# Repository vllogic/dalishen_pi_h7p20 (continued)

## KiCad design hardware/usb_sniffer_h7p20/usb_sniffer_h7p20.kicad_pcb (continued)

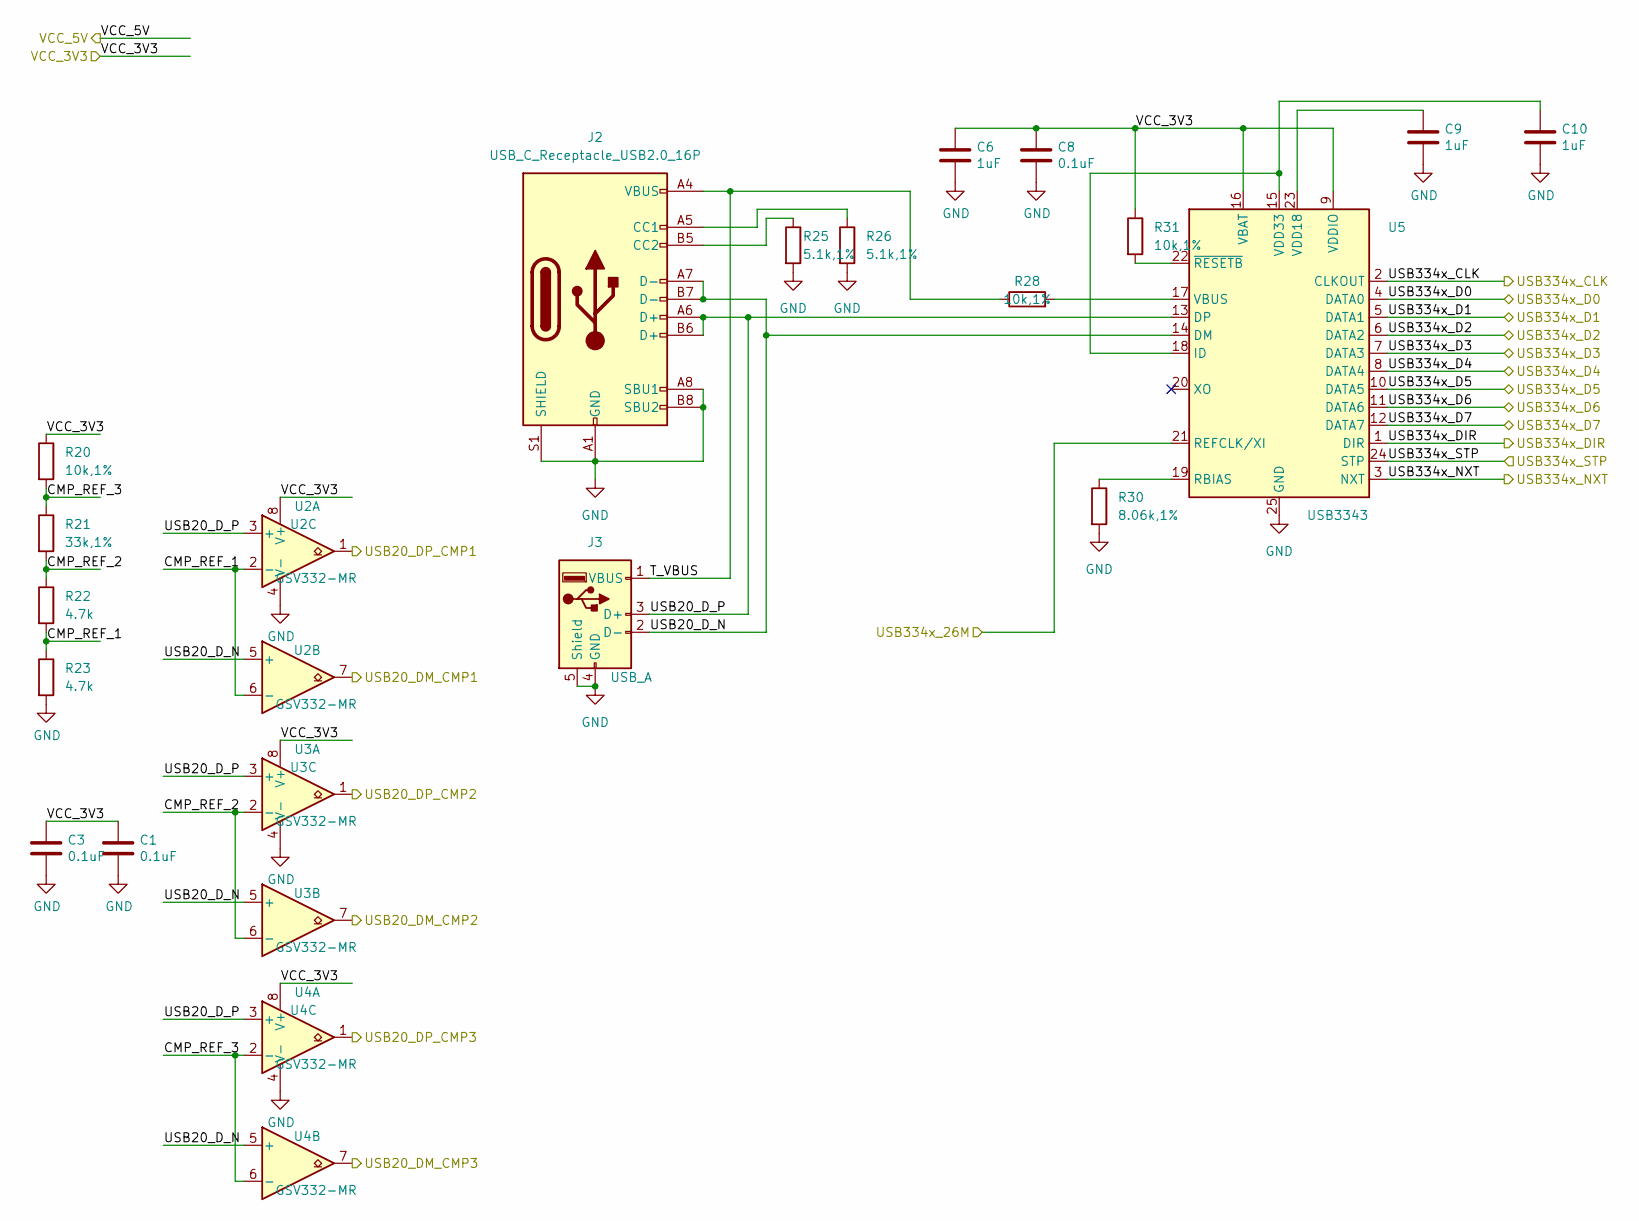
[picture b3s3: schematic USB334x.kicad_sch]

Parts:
C1, C3, C8: 0.1uF; C_0402_1005Metric
C6, C9, C10: 1uF; C_0402_1005Metric
J2: USB_C_Receptacle_USB2.0_16P; USB_C_Receptacle_16P
J3: USB_A; USB-AF_YIJIAN
R20, R28, R31: 10k,1%; R_0402_1005Metric
R21: 33k,1%; R_0402_1005Metric
R22, R23: 4.7k; R_0402_1005Metric
R25, R26: 5.1k,1%; R_0402_1005Metric
R30: 8.06k,1%; R_0402_1005Metric
U2, U3, U4: GSV332-MR; MSOP-8_3x3mm_P0.65mm
U5: USB3343; QFN-24-1EP_4x4mm_P0.5mm_EP2.6x2.6mm

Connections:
/FPGA_OUT_26M: U5.21 (REFCLK/XI); also elsewhere on the board
/USB20_DM_CMP1: U2.7; also elsewhere on the board
/USB20_DM_CMP2: U3.7; also elsewhere on the board
/USB20_DM_CMP3: U4.7; also elsewhere on the board
/USB20_DP_CMP1: U2.1; also elsewhere on the board
/USB20_DP_CMP2: U3.1; also elsewhere on the board
/USB20_DP_CMP3: U4.1; also elsewhere on the board
/USB334x/CMP_REF_1: R22.2, R23.1, U2.2 (-), U2.6 (-)
/USB334x/CMP_REF_2: R21.2, R22.1, U3.2 (-), U3.6 (-)
/USB334x/CMP_REF_3: R20.2, R21.1, U4.2 (-), U4.6 (-)
/USB334x/T_VBUS: J2.A4 (VBUS), J2.A9 (VBUS), J2.B4 (VBUS), J2.B9 (VBUS), J3.1 (VBUS), R28.1
/USB334x/USB20_D_N: J2.A7 (D-), J2.B7 (D-), J3.2 (D-), U2.5 (+), U3.5 (+), U4.5 (+), U5.14 (DM)
/USB334x/USB20_D_P: J2.A6 (D+), J2.B6 (D+), J3.3 (D+), U2.3 (+), U3.3 (+), U4.3 (+), U5.13 (DP)
/USB334x_CLK: U5.2 (CLKOUT); also elsewhere on the board
/USB334x_D0: U5.4 (DATA0); also elsewhere on the board
/USB334x_D1: U5.5 (DATA1); also elsewhere on the board
/USB334x_D2: U5.6 (DATA2); also elsewhere on the board
/USB334x_D3: U5.7 (DATA3); also elsewhere on the board
/USB334x_D4: U5.8 (DATA4); also elsewhere on the board
/USB334x_D5: U5.10 (DATA5); also elsewhere on the board
/USB334x_D6: U5.11 (DATA6); also elsewhere on the board
/USB334x_D7: U5.12 (DATA7); also elsewhere on the board
/USB334x_DIR: U5.1 (DIR); also elsewhere on the board
/USB334x_NXT: U5.3 (NXT); also elsewhere on the board
/USB334x_STP: U5.24 (STP); also elsewhere on the board
/VCC_3V3: C1.2, C3.2, C6.2, C8.2, R20.1, R31.1, U2.8 (V+), U3.8 (V+), U4.8 (V+), U5.9 (VDDIO), U5.16 (VBAT); also elsewhere on the board
GND: C1.1, C3.1, C6.1, C8.1, C9.1, C10.1, J2.A1 (GND), J2.A8 (SBU1), J2.A12 (GND), J2.B1 (GND), J2.B8 (SBU2), J2.B12 (GND), J2.S1 (SHIELD), J3.4 (GND), J3.5 (Shield), R23.2, R25.2, R26.2, R30.2, U2.4 (V-), U3.4 (V-), U4.4 (V-), U5.25 (GND); also elsewhere on the board
unnamed: J2.A5 (CC1), R26.1
unnamed: J2.B5 (CC2), R25.1
unnamed: C10.2, U5.15 (VDD33), U5.18 (ID)
unnamed: R30.1, U5.19 (RBIAS)
unnamed: R28.2, U5.17 (VBUS)
unnamed: C9.2, U5.23 (VDD18)
unnamed: R31.2, U5.22 (~RESETB)

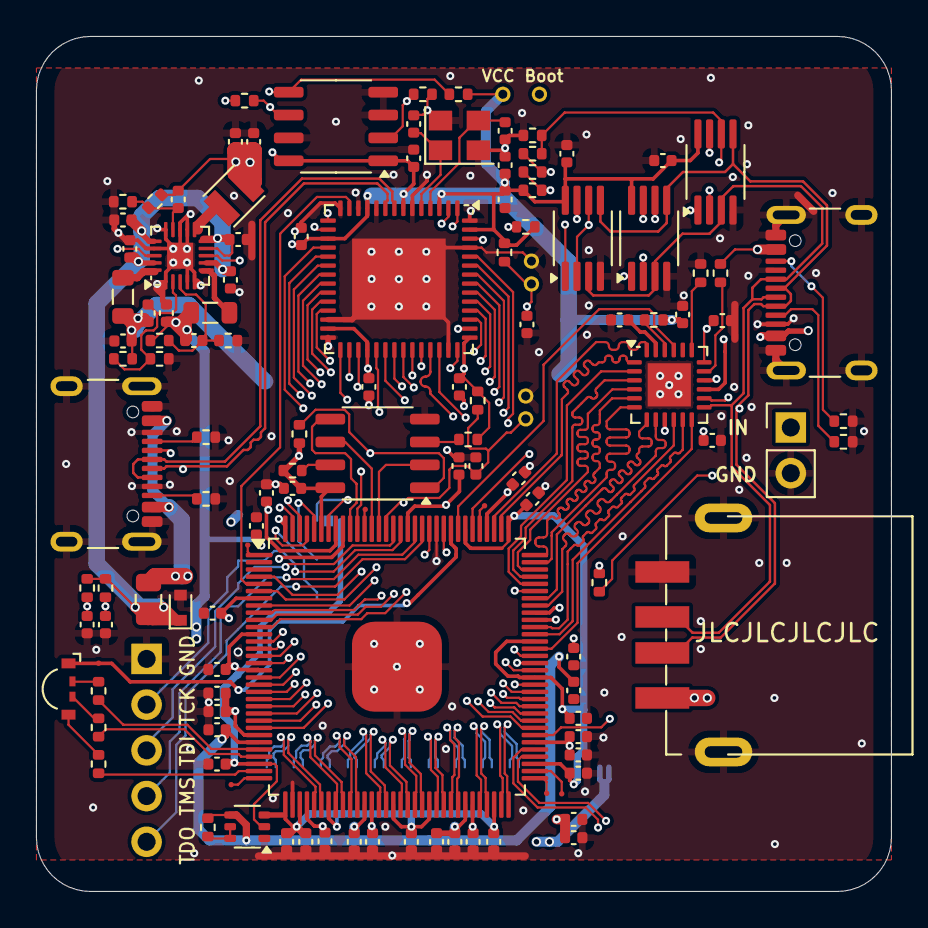
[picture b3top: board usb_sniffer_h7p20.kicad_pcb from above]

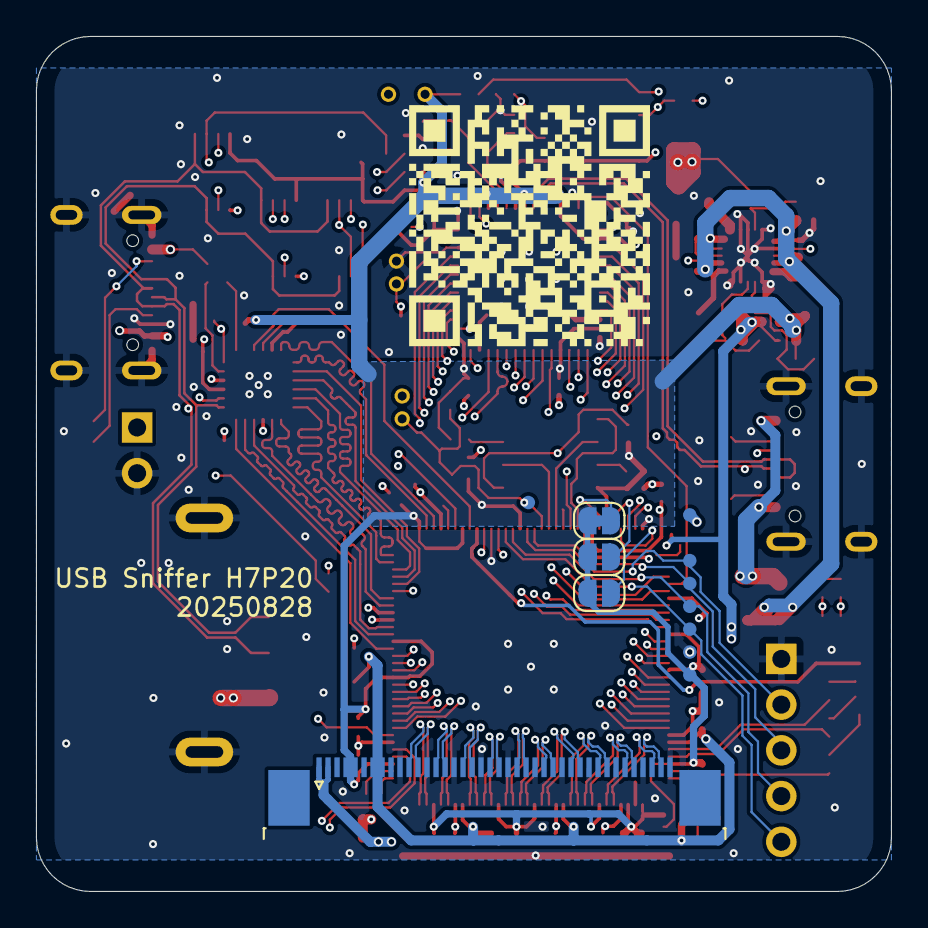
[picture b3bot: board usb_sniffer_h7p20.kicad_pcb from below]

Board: 4 copper layers, 47.5 x 47.5 mm, 139 parts (12 on the bottom side), 139 nets.

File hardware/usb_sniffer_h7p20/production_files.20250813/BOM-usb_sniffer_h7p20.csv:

Comment,Designator,Footprint,LCSC,Quantity
Trigger,J6,PinHeader_1x02_P2.54mm_Vertical,,1
0.1uF,C50,C_0402_1005Metric,,1
"5.1k,1%",R13,R_0402_1005Metric,,1
"33k,1%",R38,R_0402_1005Metric,,1
"5.1k,1%",R9,R_0402_1005Metric,,1
0.1uF,C53,C_0402_1005Metric,,1
0.1uF,C18,C_0402_1005Metric,,1
10uF,C25,C_0402_1005Metric,,1
"20k,1%",R35,R_0402_1005Metric,,1
0.1uF,C41,C_0402_1005Metric,,1
USB_C_Receptacle_USB2.0_16P,J4,USB_C_Receptacle_16P,,1
TestPoint,TP15,PinHeader_1x01_P1.00mm_Vertical,,1
LM2903A-VR,U2,MSOP-8_3x3mm_P0.65mm,,1
1uF,C38,C_0402_1005Metric,,1
TestPoint,TP16,TestPoint_Pad_D0.3mm,,1
LED_ABGR,D3,LED_RGB_Everlight_EASV3015RGBA0_Horizontal,,1
0.1uF,C51,C_0402_1005Metric,,1
4.7k,R17,R_0402_1005Metric,,1
"150k,1%",R32,R_0402_1005Metric,,1
0.1uF,C52,C_0402_1005Metric,,1
NC,C54,C_0402_1005Metric,,1
CY7C68013A-56LTX,U7,QFN-56-1EP_8x8mm_P0.5mm_EP4.5x5.2mm,,1
TestPoint,TP21,TestPoint_Pad_D0.3mm,,1
0.1uF,C61,C_0402_1005Metric,,1
TestPoint,TP18,TestPoint_Pad_D0.3mm,,1
0.1uF,C60,C_0402_1005Metric,,1
1uF,C36,C_0402_1005Metric,,1
24M,Y2,OSC_3225,,1
"5.1k,1%",R12,R_0402_1005Metric,,1
10uF,C13,C_0402_1005Metric,,1
"20k,1%",R40,R_0402_1005Metric,,1
24C32,U8,SOP-8_3.9x4.9mm_P1.27mm,,1
"4.7uH,MPL2012S4R7MHT",L3,L_0805_2012Metric,,1
H7P20N0L128-M3H1,U1,LQFP-128_14x14mm_P0.4mm_pad,,1
"20k,1%",R37,R_0402_1005Metric,,1
10uF,C37,C_0402_1005Metric,,1
220pF,C23,C_0402_1005Metric,,1
0.1uF,C59,C_0402_1005Metric,,1
0.1uF,C43,C_0402_1005Metric,,1
0.1uF,C3,C_0402_1005Metric,,1
"33k,1%",R33,R_0402_1005Metric,,1
USB_C_Receptacle_USB2.0_16P,J2,USB_C_Receptacle_16P,,1
CJ3439KDW,U9,SOT-363_SC-70-6,,1
"10k,1%",R5,R_0402_1005Metric,,1
4.7k,R23,R_0402_1005Metric,,1
TestPoint,TP17,TestPoint_Pad_D0.3mm,,1
0.1uF,C14,C_0402_1005Metric,,1
USB_A,J3,USB-AF_YIJIAN,,1
0.1uF,C58,C_0402_1005Metric,,1
10uF,C27,C_0402_1005Metric,,1
10uF,C12,C_0402_1005Metric,,1
10uF,C22,C_0402_1005Metric,,1
1uF,C6,C_0402_1005Metric,,1
"5.1k,1%",R8,R_0402_1005Metric,,1
0.1uF,C28,C_0402_1005Metric,,1
10uF,C20,C_0402_1005Metric,,1
0.1uF,C15,C_0402_1005Metric,,1
TestPoint,TP20,TestPoint_Pad_D0.3mm,,1
LM2903A-VR,U3,MSOP-8_3x3mm_P0.65mm,,1
0.1uF,C49,C_0402_1005Metric,,1
1uF,C26,C_0402_1005Metric,,1
4.7k,R16,R_0402_1005Metric,,1
0.1uF,C34,C_0402_1005Metric,,1
0.1uF,C47,C_0402_1005Metric,,1
0.1uF,C46,C_0402_1005Metric,,1
ZB25VQ16CTJG,U6,SOP-8_3.9x4.9mm_P1.27mm,,1
0.1uF,C42,C_0402_1005Metric,,1
10uF,C24,C_0402_1005Metric,,1
SMD0805B100TFT,F1,Fuse_0805_2012Metric,,1
TestPoint,TP2,PinHeader_1x01_P1.00mm_Vertical,,1
"5.1k,1%",R26,R_0402_1005Metric,,1
NC,C56,C_0402_1005Metric,,1
10uF,C39,C_0402_1005Metric,,1
CESD5V0D5,D1,D_SOD-523,,1
"33k,1%",R39,R_0402_1005Metric,,1
0.1uF,C44,C_0402_1005Metric,,1
1.5uH,L5,L_NR2520xx,,1
"10k,1%",R6,R_0402_1005Metric,,1
0.1uF,C8,C_0402_1005Metric,,1
"5.1k,1%",R3,R_0402_1005Metric,,1
0.1uF,C55,C_0402_1005Metric,,1
10uF,C17,C_0402_1005Metric,,1
"10k,1%",R20,R_0402_1005Metric,,1
TestPoint,TP4,PinHeader_1x01_P1.00mm_Vertical,,1
"5.1k,1%",R25,R_0402_1005Metric,,1
"4.7uH,MPL2012S4R7MHT",L2,L_0805_2012Metric,,1
"5.1k,1%",R4,R_0402_1005Metric,,1
220pF,C21,C_0402_1005Metric,,1
FPGA_JTAG,J1,PinHeader_1x05_P2.54mm_Vertical,,1
4.7k,R22,R_0402_1005Metric,,1
0.1uF,C45,C_0402_1005Metric,,1
1uF,C2,C_0402_1005Metric,,1
470,R7,R_0402_1005Metric,,1
0.1uF,C33,C_0402_1005Metric,,1
EA3036C,U11,QFN-20-1EP_3x3mm_P0.4mm_EP1.65x1.65mm,,1
"5.1k,1%",R18,R_0402_1005Metric,,1
CH132C,U10,QFN20C_2x2,,1
TestPoint,TP14,PinHeader_1x01_P1.00mm_Vertical,,1
12pF,C31,C_0402_1005Metric,,1
10uF,C62,C_0402_1005Metric,,1
TestPoint,TP1,PinHeader_1x01_P1.00mm_Vertical,,1
TestPoint,TP5,TestPoint_Pad_D0.3mm,,1
0.1uF,C29,C_0402_1005Metric,,1
0.1uF,C16,C_0402_1005Metric,,1
"10k,1%",R19,R_0402_1005Metric,,1
0.1uF,C4,C_0402_1005Metric,,1
NC,C19,C_0402_1005Metric,,1
4.7k,R15,R_0402_1005Metric,,1
TestPoint,TP3,PinHeader_1x01_P1.00mm_Vertical,,1
1uF,C11,C_0402_1005Metric,,1
0.1uF,C57,C_0402_1005Metric,,1
TestPoint,TP6,TestPoint_Pad_D0.3mm,,1
0.1uF,C48,C_0402_1005Metric,,1
LM2903A-VR,U4,MSOP-8_3x3mm_P0.65mm,,1
0.1uF,C35,C_0402_1005Metric,,1
"10k,1%",R24,R_0402_1005Metric,,1
"5.1k,1%",R2,R_0402_1005Metric,,1
"33k,1%",R21,R_0402_1005Metric,,1
12pF,C32,C_0402_1005Metric,,1
220pF,C30,C_0402_1005Metric,,1
NC,R31,R_0402_1005Metric,,1
"10k,1%",R34,R_0402_1005Metric,,1
TestPoint,TP7,TestPoint_Pad_D0.75mm,,1
"FFC-40P-0.5mm,NC",J5,TE_4-1734839-0_1x40-1MP_P0.5mm_Horizontal,,1
SolderJumper_2_Bridged,JP2,SolderJumper-2_P1.3mm_Bridged_RoundedPad1.0x1.5mm,,1
SolderJumper_2_Open,JP4,SolderJumper-2_P1.3mm_Open_RoundedPad1.0x1.5mm,,1
TestPoint,TP12,TestPoint_Pad_D0.75mm,,1
TestPoint,TP11,TestPoint_Pad_D0.75mm,,1
TestPoint,TP13,TestPoint_Pad_D0.75mm,,1
TestPoint,TP19,TestPoint_Pad_D0.75mm,,1
TestPoint,TP9,TestPoint_Pad_D0.75mm,,1
TestPoint,TP10,TestPoint_Pad_D0.75mm,,1
TestPoint,TP8,TestPoint_Pad_D0.75mm,,1
SolderJumper_2_Open,JP3,SolderJumper-2_P1.3mm_Open_RoundedPad1.0x1.5mm,,1

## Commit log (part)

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2025-06-02 导入几个例程
2025-06-02 主目录 readme.md
2025-06-02 增加章节号
2025-06-02 修正摄像头链接
2025-06-02 补充 交流群
2025-06-02 dalishen_pi_h7p20硬件图纸，开发中，仅备份
2025-06-02 更新硬件图
2025-06-04 硬件：usb_sniffer_h7p20，初稿，未审查
2025-06-04 增加辅助电路和优化焊盘工艺
2025-06-05 hardware\usb_sniffer_h7p20\production_files.2025605
2025-06-05 hardware\usb_sniffer_h7p20\production_files.2025605\BOM-usb_sniffer_h7p20.forJLC.csv
2025-06-06 docs
2025-06-06 调整上电顺序为 5V -> core 0.95V -> vccaux 1.8V -> vccio
2025-06-06 更新丝印
2025-06-06 move
2025-06-06 例程文件夹增加目标板名称
2025-06-06 还原verilog，配置相关IO
2025-06-07 [usb_sniffer_h7p20]增加JTAG排针，增加产品页二维码
2025-06-15 [usb_sniffer_h7p20] 结构优化与验证
2025-06-16 [usb_sniffer_h7p20] 修复USB3343参考时钟电路错误；修复USB3343 RESET脚上拉错误
2025-06-16 [usb_sniffer_h7p20.ataradov.usb_sniffer] 从68013引入时钟48M，PLL输出26M给USB3343，从而省去一个无源晶振
2025-06-16 [usb_sniffer_h7p20] 68013的eeprom增加boot点，用于二次更新68013固件
2025-06-16 [usb_sniffer_h7p20.ataradov.usb_sniffer] 部分逻辑增加default
2025-06-17 [usb_sniffer_h7p20] 预留外部触发接口，优化布局，支持M4隔离柱
2025-06-17 [usb_sniffer_h7p20.ataradov.usb_sniffer] cmp_dm_i cmp_dp_i 启用内置上拉
2025-06-17 [docs] add LM2903A-VR.PDF
2025-06-18 [usb_sniffer_h7p20] 使用USB5V驱动LM2903
2025-06-19 [usb_sniffer_h7p20] 移除NC器件，更换LM2903A-VR，双螺丝孔固定
2025-06-19 readme.md
2025-06-20 [usb_sniffer_h7p20] 优化USB封装精度，优化定位孔精度
2025-06-20 [usb_sniffer_h7p20] production_files.2025620
2025-06-21 [dalishen_pi_h7p20] backup
2025-06-21 [usb_sniffer_h7p20] 优化上电
2025-06-22 [usb_sniffer_h7p20] USB3343兼容CH132F，作相关调整
2025-06-22 [dalishen_pi_h7p20] 原理图初稿
2025-06-23 [dalishen_pi_h7p20] 原理图预审
2025-06-23 [dalishen_pi_h7p20] CRST电容增大、MIPI CSI使用同一bank
2025-06-24 [dalishen_pi_h7p20] layout done
2025-06-24 [dalishen_pi_h7p20] 样板
2025-06-25 [usb_sniffer_h7p20] 优化局部走线
2025-06-25 [usb_sniffer_h7p20] 更新Gerber
2025-06-30 BOM-dalishen_pi_h7p20.JLC.csv
2025-07-07 [dalishen_pi_h7p20] YT8531C需增加一个电感；需从XO引入时钟，XI接地； 剩余样板需换贴YC8531DC或者手工割线加电感。千兆协商通过。 LAYOUT优化
2025-07-08 与 usb_sniffer_h7p20.ataradov.usb_sniffer 同步
2025-07-08 [dalishen_pi_h7p20] USB协议分析仪功能可用，不包括JK部分
2025-07-08 [dalishen_pi_h7p20] 由于JTAG口在LQFP128封装上无法作为IO使用，故移除SE0，J, K状态电路
2025-07-11 [dalishen_pi_h7p20] production_files.20250711 不贴片，仅用于电源排查
2025-07-13 [dalishen_pi_h7p20] 新建arm_rgmii工程，用于测试SOC及RGMII接口
2025-07-13 [dalishen_pi_h7p20] 分配IO
2025-07-13 [dalishen_pi_h7p20] 两个双排针的VCC脚通过短接点连接3.3V，预留给其他扩展模块供电的能力。
2025-07-13 [dalishen_pi_h7p20]从 ip_core\ethernet_mac_v3\example\P0_P2\EthernetMac_example_h7.zip 导入M3工程
2025-07-13 [dalishen_pi_h7p20] RGMII千兆可PING通，变动如下： 1. EthernetMAC_v3.v中的BASE_ADDR需改为0x00000000 2. MDIO初始参数，讲RGMII电平从1.8V改为3.3V 3. 修改DEST_MAC_ADDR，调整为对接PC的实际MAC
2025-07-17 [dalishen_pi_h7p20] 优化LAYOUT
2025-08-08 将USB3343替换为CH132C，ULPI时钟由FPGA产生
2025-08-11 [dalishen_pi_h7p20] 使用无工艺边设计
2025-08-12 [dalishen_pi_h7p20] 引出串口，对接板载调试器的串口，LOG功能可用
2025-08-12 [usb_sniffer_h7p20] 适配铝合金外壳、更换CH132C
2025-08-13 [usb_sniffer_h7p20] 待审查
2025-08-13 [usb_sniffer_h7p20] 20250813 打样
2025-08-13 [usb_sniffer_h7p20.ataradov.usb_sniffer] 适配新版本硬件，待测试
2025-08-18 [usb_sniffer_h7p20] CH132C测试无数据，回退USB3343
2025-08-18 [usb_sniffer_h7p20] 统一使用P25Q64SH-SSH-IR
2025-08-19 [dalishen_pi_h7p20] 备份
2025-08-21 [dalishen_pi_h7p20] production_files.20250820
2025-08-22 [dalishen_pi_h7p20] production_files.20250820 新增保险丝
2025-08-24 [usb_sniffer_h7p20] 换GSV332-MR，待测试
2025-08-27 [usb_sniffer_h7p20] production_files.20250828
2025-09-13 [usb_sniffer_h7p20.ataradov.usb_sniffer] usb_sniffer_bin.acf
2025-09-14 [dalishen_pi_h7p20] A母换SMT型号
2025-09-16 [dalishen_pi_h7p20] 68013替换为双USB3343
2025-09-16 [dalishen_pi_h7p20] 增加I2C小屏，增加两个测试IO
2025-09-17 [dalishen_pi_h7p20] 待review
2025-09-17 [dalishen_pi_h7p20] 打样
2025-09-22 [dalishen_pi_h7p20]自锁开关脚位修正
2026-05-31 [dalishen_pi_h7p20] 生成方波
2026-06-09 [usb_sniffer_2]硬件图纸公开
2026-06-09 add LICENSE
